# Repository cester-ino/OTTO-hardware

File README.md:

## OTTO-project
Hardware prototype for the [OTTO Synthesizer by Topisani](https://github.com/topisani/OTTO "OTTO Synthesizer by Topisani")

*10x10 silicone buttons with led backlight*

Main features

#### Mainboard
- ILI9341 based TFT 2.8" TFT screen.
- 4 low profile clickable encoders
- 40 function keys
- STM32F103VET6 mcu
- Raspberry GPIO connector
- connects to all the various boards
- expansion headers

#### Power board
- 2A 5-16V DC input & 500mah micro usb input
- [MAX8903A](https://datasheets.maximintegrated.com/en/ds/MAX8903-MAX8903Y.pdf "MAX8903A") 1s Lipo charger IC with path management
- 5V 2A DC-DC boost converter ([TPS61090](http://www.ti.com/lit/ds/symlink/tps61090.pdf "TPS61090")) & 3V3 700mah LDO ([XC6210](https://www.torexsemi.com/file/xc6210/XC6210.pdf "XC6210"))
- [MAX17048](https://datasheets.maximintegrated.com/en/ds/MAX17048-MAX17049.pdf "MAX17048") 1s lipo fuel gauge, connected via i2c to the raspberry
- [pi_power](https://github.com/craic/pi_power "pi_power") circuit for monitoring and control boot and shutdown routine

#### Audio Board
- SGTL5000 Audio Codec
- Electret microphone amp circuit
- LM4860 speaker amplifier
- 1 TRS jack line IN
- 1 TRS jack line OUT
- 1 Headphone IN

#### Keyboard
- 2 octaves keyboard with 16 keys bottom row
- expansion headers
- 16 addressable rgb leds

those specs refer to the tactile buttons version, but a led backlight button version is in the works too.

*one of the first design iteration*

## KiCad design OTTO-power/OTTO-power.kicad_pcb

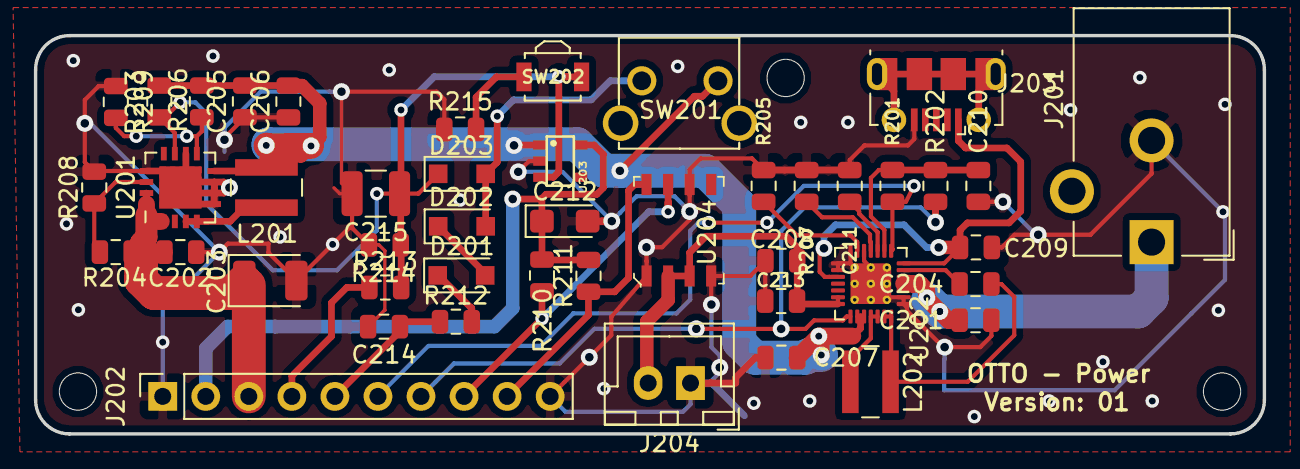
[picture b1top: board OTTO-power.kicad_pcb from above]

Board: 2 copper layers, 72.5 x 23.5 mm, 45 parts (0 on the bottom side), 28 nets.

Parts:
C201, C202, C210: 2.2uf; C_0805_2012Metric
C203: 100uf; CP_EIA-3528-21_Kemet-B
C204: 1uf; C_0805_2012Metric
C205, C207, C208: 10uf; C_0805_2012Metric
C206, C213, C214: 0.1uf; C_0805_2012Metric
C209: 4.7uf; C_0805_2012Metric
C211: 0.15uf; C_0805_2012Metric
C212: 10uf; CP_EIA-3216-18_Kemet-A
C215: 100uf; C_1210_3225Metric
D201, D202, D203: IN4001; D_SOD-123F
J201: Barrel_Jack; BarrelJack_CUI_PJ-102AH_Horizontal
J202: Conn_01x10; PinSocket_1x10_P2.54mm_Vertical
J203: USB_B_Micro; USB_Micro-B_Molex-105017-0001
J204: battery; JST_XH_B02B-XH-A_1x02_P2.50mm_Vertical
L201: 6.8uH; L_Wuerth_MAPI-4020
L202: 3.3uH; L_Wuerth_MAPI-4020
R201, R202, R210, R211, R214: 100K; R_0805_2012Metric
R203, R208: 200K; R_0805_2012Metric
R204, R206: 1.87M; R_0805_2012Metric
R205: 1.2K; R_0805_2012Metric
R207: 3K; R_0805_2012Metric
R209: 340K; R_0805_2012Metric
R212, R213: 10K; R_0805_2012Metric
R215: 1K; R_0805_2012Metric
SW201: SW_Push; SKHHLVA010
SW202: SW_reset; SW_SPST_B3U-3000P
U201: TPS61090; QFN-16-1EP_4x4mm_P0.65mm_EP2.5x2.5mm
U202: MAX8903A; QFN-28-1EP_4x4mm_P0.4mm_EP2.4x2.4mm_ThermalVias
U203: XC6210; SOT25
U204: MAX17048; TDFN-8-1EP

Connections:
3V3: C212.1, J202.2, R210.2, R211.2, U203.5
5V: C202.2, C203.1, J202.3, R204.2, U201.1, U201.15, U201.16
BATT+: C208.2, C213.2, J204.2, U202.20, U202.21, U204.2, U204.3
CHG_OUT: J202.7, R202.1, U202.22
DC: C201.1, J201.1, U202.3, U202.4, U202.5
DOK_OUT: J202.6, R201.1, U202.8
EN_PI: C215.1, D203.1, R203.1, R213.1, R214.2, SW202.2, U201.11, U203.3
GNDA: C201.2, C202.1, C203.2, C205.1, C206.1, C207.1, C208.1, C209.1, C210.1, C211.1, C212.2, C213.1, C214.2, C215.2, J201.2, J202.1, J202.10, J203.5, J204.1, R205.1, R207.1, R208.1, R209.1, R214.1, R215.1, U201.5, U201.6, U201.7, U201.10, U201.13, U201.17, U202.1, U202.2, U202.12, U202.14, U202.15, U202.16, U202.29, U203.2, U204.1, U204.4, U204.6
unnamed: C204.1, U202.6
unnamed: C204.2, L202.2, U202.27, U202.28
unnamed: C211.2, U202.10
unnamed: D201.1, R212.1
unnamed: D201.2, D202.1
unnamed: D202.2, D203.2, SW201.2
unnamed: L201.1, U201.3, U201.4
unnamed: L202.1, U202.25, U202.26
unnamed: R204.1, R208.2, U201.14
unnamed: R205.2, U202.13
unnamed: R206.1, R209.2, U201.9
unnamed: R207.2, U202.11
unnamed: R215.2, SW202.1
OUT_PIN: J202.4, R213.2
SCL: J202.8, R210.1, U204.7
SDA: J202.9, R211.1, U204.8
SENSE_PIN: C214.1, J202.5, R212.2
SYS: C205.2, C206.2, C207.2, L201.2, R203.2, R206.2, SW201.1, U201.8, U202.23, U202.24, U203.1
USB: C209.2, J203.1, U202.7, U202.17
VL: C210.2, R201.2, R202.2, U202.9

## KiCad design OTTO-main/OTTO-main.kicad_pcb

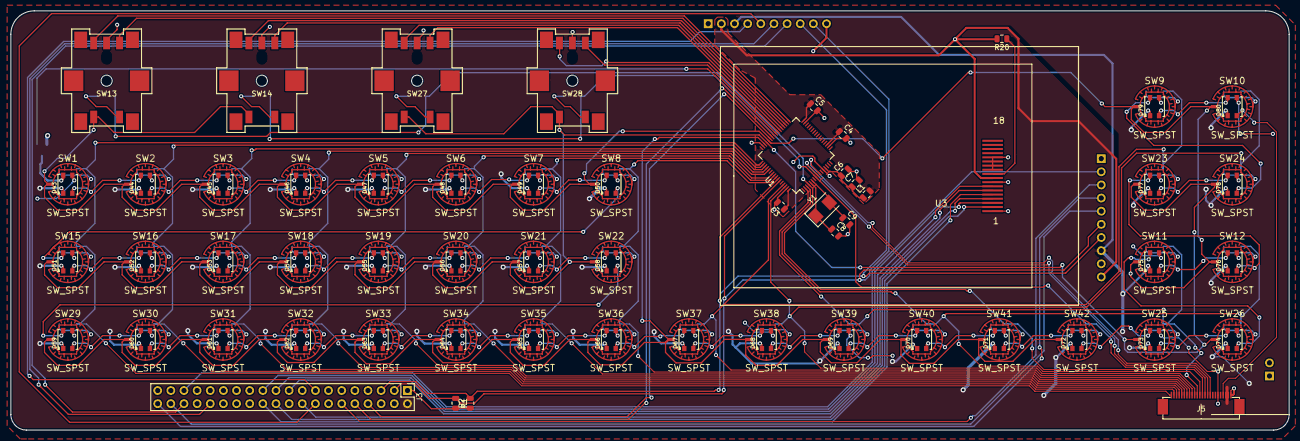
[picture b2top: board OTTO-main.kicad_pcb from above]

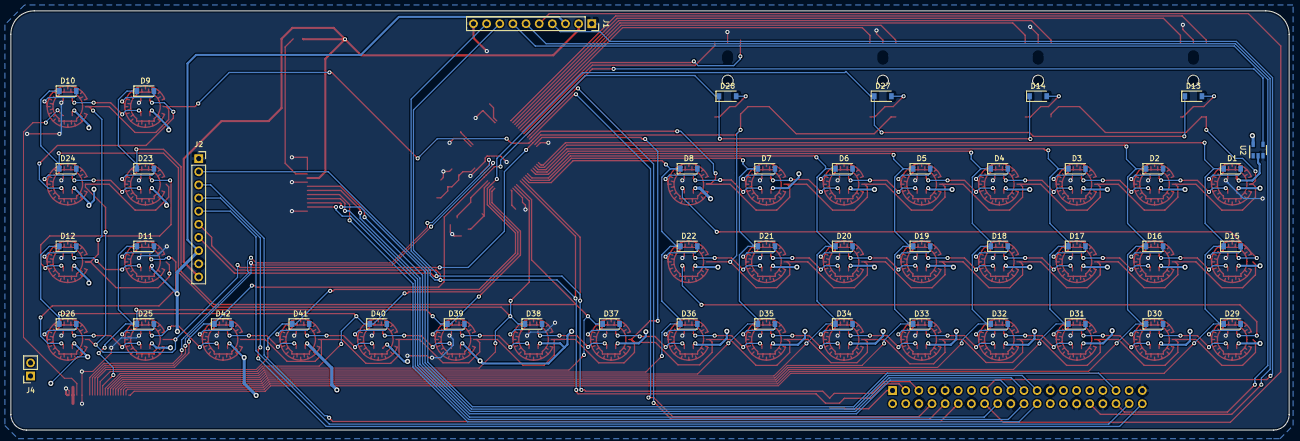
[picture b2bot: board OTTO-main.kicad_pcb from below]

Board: 4 copper layers, 247.0 x 81.0 mm, 142 parts (46 on the bottom side), 135 nets.

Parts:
C3, C4, C5, C6: 1uf; C_0805_2012Metric
C7: 10nf; C_0805_2012Metric
C8, C9: 22pf; C_0805_2012Metric
D1, D2, D3, D4, D5, D6, D7, D8, D9, D10, D11, D12, D15, D16, D17, D18, D19, D20, D21, D22, D23, D24, D25, D26, D29, D30, D31, D32, D33, D34, D35, D36, D37, D38, D39, D40, D41, D42: D_ALT; D_SOD-123
D13, D14, D27, D28: 1N4148; D_SOD-123
D43, D44, D45, D46, D47, D48, D49, D50, D51, D52, D53, D54, D55, D56, D57, D58, D59, D60, D61, D62, D63, D64, D65, D66, D67, D68, D69, D70, D71, D72, D73, D74, D75, D76, D77, D78, D79, D80: WS2812B; WS2812B_3535
J1: POWER_BOARD; PinSocket_1x10_P2.54mm_Vertical
J2: AUDIO_BOARD; PinSocket_1x10_P2.54mm_Vertical
J3: Raspberry_Pi_2_3; PinHeader_2x20_P2.54mm_Vertical
J4: MICROPHONE; PinSocket_1x02_P2.54mm_Vertical
J5: Conn_01x24; JUSHUO_AFC07-S24FCC-00
L1: 30ohm; C_0805_2012Metric
R1, R2: 4.7K; R_0805_2012Metric
R20: 3.9; R_0805_2012Metric
SW1, SW2, SW3, SW4, SW5, SW6, SW7, SW8, SW9, SW10, SW11, SW12, SW15, SW16, SW17, SW18, SW19, SW20, SW21, SW22, SW23, SW24, SW25, SW26, SW29, SW30, SW31, SW32, SW33, SW34, SW35, SW36, SW37, SW38, SW39, SW40, SW41, SW42: SW_SPST; SILICONE_BUTTON_10MM_4X4WIDE
SW13, SW14, SW27, SW28: Rotary_Encoder_Switch; PEC11S-929K-S0015
U1: STM32F103RETx; LQFP-64_10x10mm_P0.5mm
U2: 74AHCT1G125; SOT-23-5
U3: ILI9341; ILI_DISPLAY
Y1: 8mhz; Crystal_SMD_5032-2Pin_5.0x3.2mm

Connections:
3V3: C3.1, C4.1, C5.1, J1.2, J2.10, L1.2, R20.2, U1.19, U1.32, U1.48, U1.64, U3.9
5V: D43.1, D44.1, D45.1, D46.1, D47.1, D48.1, D49.1, D50.1, D51.1, D52.1, D53.1, D54.1, D55.1, D56.1, D57.1, D58.1, D59.1, D60.1, D61.1, D62.1, D63.1, D64.1, D65.1, D66.1, D67.1, D68.1, D69.1, D70.1, D71.1, D72.1, D73.1, D74.1, D75.1, D76.1, D77.1, D78.1, D79.1, D80.1, J1.3, J2.8, J3.2, J5.22, J5.23
BCLK: J2.3, J3.12
CE0: J3.24, U3.5
CHG_OUT: J1.7, J3.36
COL1: D1.1, D15.1, D29.1, J5.1, U1.49
COL2: D2.1, D16.1, D30.1, J5.2, U1.50
COL3: D3.1, D17.1, D31.1, J5.3, U1.51
COL4: D4.1, D18.1, D32.1, J5.4, U1.52
COL5: D5.1, D19.1, D33.1, J5.5, U1.53
COL6: D6.1, D20.1, D34.1, J5.6, U1.55
COL7: D7.1, D21.1, D35.1, J5.7, U1.56
COL8: D8.1, D22.1, D36.1, J5.8, U1.57
COL9: D9.1, D23.1, D37.1, J5.9, U1.61
COL10: D10.1, D24.1, D38.1, J5.10, U1.62
COL11: D11.1, D25.1, D39.1, J5.11, U1.2
COL12: D12.1, D26.1, D40.1, J5.12, U1.3
COL13: D13.1, D27.1, D41.1, J5.13, U1.4
COL14: D14.1, D28.1, D42.1, J5.14, U1.8
DOK_OUT: J1.6, J3.32
DOUT1: D52.2, D53.4
DOUT2: D66.2, D67.4
ENC1_A: SW13.A, U1.34
ENC1_B: SW13.B, U1.33
ENC2_A: SW14.A, U1.36
ENC2_B: SW14.B, U1.35
ENC3_A: SW27.A, U1.38
ENC3_B: SW27.B, U1.37
ENC4_A: SW28.A, U1.40
ENC4_B: SW28.B, U1.39
GND: C3.2, C4.2, C5.2, C6.2, C7.2, C8.2, C9.2, D43.3, D44.3, D45.3, D46.3, D47.3, D48.3, D49.3, D50.3, D51.3, D52.3, D53.3, D54.3, D55.3, D56.3, D57.3, D58.3, D59.3, D60.3, D61.3, D62.3, D63.3, D64.3, D65.3, D66.3, D67.3, D68.3, D69.3, D70.3, D71.3, D72.3, D73.3, D74.3, D75.3, D76.3, D77.3, D78.3, D79.3, D80.3, J1.1, J1.10, J2.1, J2.9, J3.6, J3.9, J3.14, J3.20, J3.25, J3.30, J3.34, J3.39, J5.19, J5.24, SW13.C, SW14.C, SW27.C, SW28.C, U1.12, U1.18, U1.31, U1.47, U1.63, U2.3, U3.1, U3.8, U3.11, U3.12, U3.13, U3.14
GPIO24: J3.18, U3.4
GPIO25: J3.22, U3.2
I2S_RX: J2.4, J3.40
I2S_TX: J2.5, J3.38
KBLED: D80.2, J5.21
LEDIN: U1.41, U2.4
LR_CLK: J2.2, J3.35
MISO_0: J3.21, U3.7
MOSI_0: J3.19, U3.6
unnamed: C6.1, C7.1, L1.1, U1.13
unnamed: D1.2, SW1.2
unnamed: D2.2, SW2.2
unnamed: D3.2, SW3.2
unnamed: D4.2, SW4.2
unnamed: D5.2, SW5.2
unnamed: D6.2, SW6.2
unnamed: D7.2, SW7.2
unnamed: D8.2, SW8.2
unnamed: D9.2, SW9.2
unnamed: D10.2, SW10.2
unnamed: D11.2, SW11.2
unnamed: D12.2, SW12.2
unnamed: D13.2, SW13.S1
unnamed: D14.2, SW14.S1
unnamed: D15.2, SW15.2
unnamed: D16.2, SW16.2
unnamed: D17.2, SW17.2
unnamed: D18.2, SW18.2
unnamed: D19.2, SW19.2
unnamed: D20.2, SW20.2
unnamed: D21.2, SW21.2
unnamed: D22.2, SW22.2
unnamed: D23.2, SW23.2
unnamed: D24.2, SW24.2
unnamed: D25.2, SW25.2
unnamed: D26.2, SW26.2
unnamed: D27.2, SW27.S1
unnamed: D28.2, SW28.S1
unnamed: D29.2, SW29.2
unnamed: D30.2, SW30.2
unnamed: D31.2, SW31.2
unnamed: D32.2, SW32.2
unnamed: D33.2, SW33.2
unnamed: D34.2, SW34.2
unnamed: D35.2, SW35.2
unnamed: D36.2, SW36.2
unnamed: D37.2, SW37.2
unnamed: D38.2, SW38.2
unnamed: D39.2, SW39.2
unnamed: D40.2, SW40.2
unnamed: D41.2, SW41.2
unnamed: D42.2, SW42.2
unnamed: D43.2, D44.4
unnamed: D43.4, U2.2
unnamed: D44.2, D45.4
unnamed: D45.2, D46.4
unnamed: D46.2, D47.4
unnamed: D47.2, D48.4
unnamed: D48.2, D49.4
unnamed: D49.2, D50.4
unnamed: D50.2, D51.4
unnamed: D51.2, D52.4
unnamed: D53.2, D54.4
unnamed: D54.2, D55.4
unnamed: D55.2, D56.4
unnamed: D56.2, D57.4
unnamed: D57.2, D58.4
unnamed: D58.2, D59.4
unnamed: D59.2, D60.4
unnamed: D60.2, D61.4
unnamed: D61.2, D62.4
unnamed: D62.2, D63.4
unnamed: D63.2, D64.4
unnamed: D64.2, D65.4
unnamed: D65.2, D66.4
unnamed: D67.2, D68.4
unnamed: D68.2, D69.4
unnamed: D69.2, D70.4
unnamed: D70.2, D71.4
unnamed: D71.2, D72.4
unnamed: D72.2, D73.4
unnamed: D73.2, D74.4
unnamed: D74.2, D75.4
unnamed: D75.2, D76.4
unnamed: D76.2, D77.4
unnamed: D77.2, D78.4
unnamed: D78.2, D79.4
unnamed: D79.2, D80.4
unnamed: J3.1, R1.2, R2.1
unnamed: R20.1, U3.10
OSC_IN: C8.1, U1.5, Y1.1
OSC_OUT: C9.1, U1.6, Y1.2
OUT_PIN: J1.4, J3.15
ROW1: SW1.1, SW2.1, SW3.1, SW4.1, SW5.1, SW6.1, SW7.1, SW8.1, SW9.1, SW10.1, SW11.1, SW12.1, SW13.S2, SW14.S2, U1.44
ROW2: SW15.1, SW16.1, SW17.1, SW18.1, SW19.1, SW20.1, SW21.1, SW22.1, SW23.1, SW24.1, SW25.1, SW26.1, SW27.S2, SW28.S2, U1.45
ROW3: SW29.1, SW30.1, SW31.1, SW32.1, SW33.1, SW34.1, SW35.1, SW36.1, SW37.1, SW38.1, SW39.1, SW40.1, SW41.1, SW42.1, U1.46
ROW4: J5.15, U1.9
ROW5: J5.16, U1.10
SCL: J1.8, J2.7, J3.5, R2.2, U1.58
SCLK_0: J3.23, U3.3
SDA: J1.9, J2.6, J3.3, R1.1, U1.59
SENSE_PIN: J1.5, J3.16
UART_RXD: J3.10, U1.42
UART_TXD: J3.8, U1.43

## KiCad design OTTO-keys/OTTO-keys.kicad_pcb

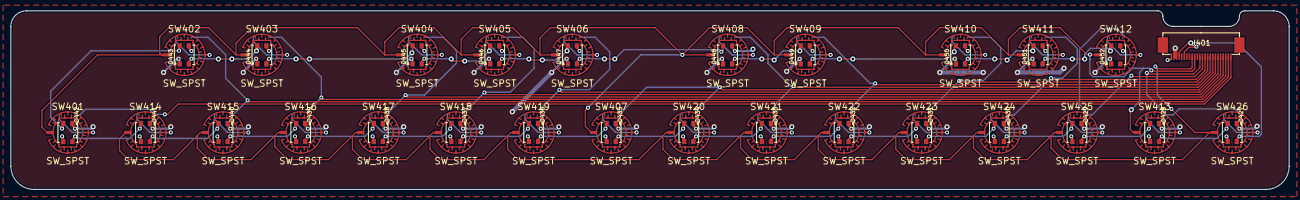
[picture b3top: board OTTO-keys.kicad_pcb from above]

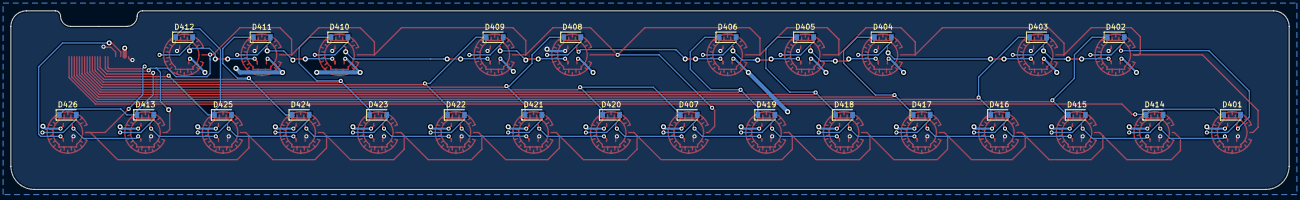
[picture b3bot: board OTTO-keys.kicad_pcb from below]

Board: 2 copper layers, 247.0 x 34.5 mm, 79 parts (26 on the bottom side), 69 nets.

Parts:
D401, D402, D403, D404, D405, D406, D407, D408, D409, D410, D411, D412, D413, D414, D415, D416, D417, D418, D419, D420, D421, D422, D423, D424, D425, D426: D_ALT; D_SOD-123
D427, D428, D429, D430, D431, D432, D433, D434, D435, D436, D437, D438, D439, D440, D441, D442, D443, D444, D445, D446, D447, D448, D449, D450, D451, D452: WS2812B; WS2812B_3535
J401: Conn_01x24; JUSHUO_AFC07-S24FCC-00
SW401, SW402, SW403, SW404, SW405, SW406, SW407, SW408, SW409, SW410, SW411, SW412, SW413, SW414, SW415, SW416, SW417, SW418, SW419, SW420, SW421, SW422, SW423, SW424, SW425, SW426: SW_SPST; SILICONE_BUTTON_10MM_4X4WIDE

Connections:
5V: D427.1, D428.1, D429.1, D430.1, D431.1, D432.1, D433.1, D434.1, D435.1, D436.1, D437.1, D438.1, D439.1, D440.1, D441.1, D442.1, D443.1, D444.1, D445.1, D446.1, D447.1, D448.1, D449.1, D450.1, D451.1, D452.1, J401.22, J401.23
COL1: D401.1, D414.1, J401.1
COL2: D402.1, D415.1, J401.2
COL3: D403.1, D416.1, J401.3
COL4: D404.1, D417.1, J401.4
COL5: D405.1, D418.1, J401.5
COL6: D406.1, D419.1, J401.6
COL7: D407.1, D420.1, J401.7
COL8: D408.1, D421.1, J401.8
COL9: D409.1, D422.1, J401.9
COL10: D410.1, D423.1, J401.10
COL11: D411.1, D424.1, J401.11
COL12: D412.1, D425.1, J401.12
COL13: D413.1, D426.1, J401.13
DOUT1: D440.2, D441.4
GND: D427.3, D428.3, D429.3, D430.3, D431.3, D432.3, D433.3, D434.3, D435.3, D436.3, D437.3, D438.3, D439.3, D440.3, D441.3, D442.3, D443.3, D444.3, D445.3, D446.3, D447.3, D448.3, D449.3, D450.3, D451.3, D452.3, J401.19, J401.24
KBLED: D427.4, J401.21
unnamed: D401.2, SW401.2
unnamed: D402.2, SW402.2
unnamed: D403.2, SW403.2
unnamed: D404.2, SW404.2
unnamed: D405.2, SW405.2
unnamed: D406.2, SW406.2
unnamed: D407.2, SW407.2
unnamed: D408.2, SW408.2
unnamed: D409.2, SW409.2
unnamed: D410.2, SW410.2
unnamed: D411.2, SW411.2
unnamed: D412.2, SW412.2
unnamed: D413.2, SW413.2
unnamed: D414.2, SW414.2
unnamed: D415.2, SW415.2
unnamed: D416.2, SW416.2
unnamed: D417.2, SW417.2
unnamed: D418.2, SW418.2
unnamed: D419.2, SW419.2
unnamed: D420.2, SW420.2
unnamed: D421.2, SW421.2
unnamed: D422.2, SW422.2
unnamed: D423.2, SW423.2
unnamed: D424.2, SW424.2
unnamed: D425.2, SW425.2
unnamed: D426.2, SW426.2
unnamed: D427.2, D428.4
unnamed: D428.2, D429.4
unnamed: D429.2, D430.4
unnamed: D430.2, D431.4
unnamed: D431.2, D432.4
unnamed: D432.2, D433.4
unnamed: D433.2, D434.4
unnamed: D434.2, D435.4
unnamed: D435.2, D436.4
unnamed: D436.2, D437.4
unnamed: D437.2, D438.4
unnamed: D438.2, D439.4
unnamed: D439.2, D440.4
unnamed: D441.2, D442.4
unnamed: D442.2, D443.4
unnamed: D443.2, D444.4
unnamed: D444.2, D445.4
unnamed: D445.2, D446.4
unnamed: D446.2, D447.4
unnamed: D447.2, D448.4
unnamed: D448.2, D449.4
unnamed: D449.2, D450.4
unnamed: D450.2, D451.4
unnamed: D451.2, D452.4
ROW4: J401.15, SW401.1, SW402.1, SW403.1, SW404.1, SW405.1, SW406.1, SW407.1, SW408.1, SW409.1, SW410.1, SW411.1, SW412.1, SW413.1
ROW5: J401.16, SW414.1, SW415.1, SW416.1, SW417.1, SW418.1, SW419.1, SW420.1, SW421.1, SW422.1, SW423.1, SW424.1, SW425.1, SW426.1

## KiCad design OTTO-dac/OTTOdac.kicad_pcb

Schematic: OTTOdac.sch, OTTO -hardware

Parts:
C101, C104, C106, C109, C110, C112, C113, C119: 2.2uf; C_0805_2012Metric
C102, C103, C105, C108, C117, C118: 0.1uf; C_0805_2012Metric
C107, C116: 0.1uf; CP_EIA-2012-12_Kemet-R
C111: 1uf; CP_EIA-3216-18_Kemet-A
C114, C115: 220uf; CP_Elec_5x5.9
J101: SJ1-42536-SMT; PJ-393-7A; MPN SJ1-42536-SMT
J102: Audio_IN; PJ-237-6A
J103: Audio_OUT; PJ-237-6A
J104: Speaker; JST_XH_B02B-XH-A_1x02_P2.50mm_Vertical; MPN XH-B02B
J105: Conn_01x10; PinHeader_1x10_P2.54mm_Vertical
L101: 600; Fuse_0805_2012Metric
MK101: Microphone; PinHeader_1x02_P2.54mm_Vertical
R101, R102: 100K; R_0805_2012Metric
R103, R105: 10K; R_0805_2012Metric
R104, R106, R107: 1K; R_0805_2012Metric
R108: 2.2K; R_0805_2012Metric
U101: AMS1117-3.3; SOT-223-3_TabPin2
U102: SGTL5000; QFN-32-NXP-SGTL5000
X101: XO32; Oscillator_SMD_Abracon_ASV-4Pin_7.0x5.1mm

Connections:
+3V3: C101.1, C102.1, C103.1, C108.1, J105.10, L101.1, U101.3 (VI), U102.20, X101.1, X101.4
+5V: C107.1, J105.8, R101.1; also elsewhere on the board
GNDREF: C101.2, C102.2, C103.2, C104.2, C105.2, C106.2, C107.2, C108.2, C116.2, C117.1, C119.2, J101.4, J102.1, J103.1, J105.1, J105.9, MK101.1, R107.1, U101.1 (GND), U102.1, U102.3, U102.7, U102.31, U102.32, U102.33, X101.2; also elsewhere on the board
HPL: C114.2, J101.2, R104.1
HPR: C115.2, J101.3, R106.1, R107.2
MIC: C118.2, J101.1, R108.2
unnamed: C104.1, C105.1, L101.2, U102.5
unnamed: C106.1, U101.2 (VO), U102.30
unnamed: C109.1, U102.14
unnamed: C109.2, J102.2
unnamed: C110.1, U102.13
unnamed: C110.2, J102.3
unnamed: C111.1, R105.1
unnamed: C111.2, R104.2, R106.2
unnamed: C112.1, U102.11
unnamed: C112.2, J103.3
unnamed: C113.1, U102.12
unnamed: C113.2, J103.2
unnamed: C114.1, U102.6
unnamed: C115.1, U102.2
unnamed: C117.2, U102.10
unnamed: C118.1, U102.15
unnamed: C119.1, R108.1, U102.16
unnamed: J101.6, R101.2, R102.2
unnamed: J101.8, MK101.2
unnamed: R103.2, R105.2
unnamed: U102.21, X101.3
PIN3: J105.6, U102.27
PIN5: J105.7, U102.29
PIN12: J105.3, U102.24
PIN35: J105.2, U102.23
PIN38: J105.5, U102.26
PIN40: J105.4, U102.25

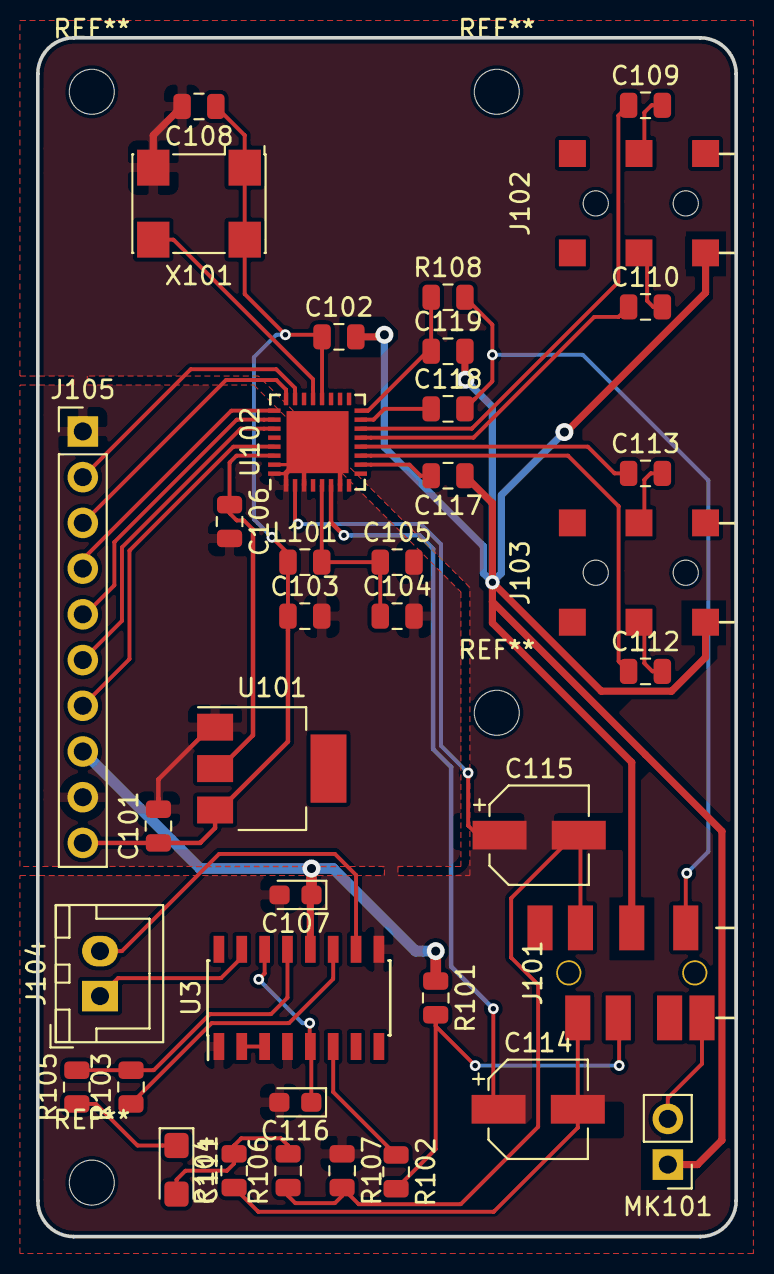
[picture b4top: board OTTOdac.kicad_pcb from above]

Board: 2 copper layers, 38.8 x 66.6 mm, 38 parts (0 on the bottom side), 35 nets.

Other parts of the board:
U3: LM4860; SOIC-16_3.9x9.9mm_P1.27mm

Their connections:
+5V: U3.12; also elsewhere on the board
GNDREF: U3.1, U3.4, U3.9; also elsewhere on the board
unnamed: U3.5, U3.14
unnamed: U3.2, U3.3

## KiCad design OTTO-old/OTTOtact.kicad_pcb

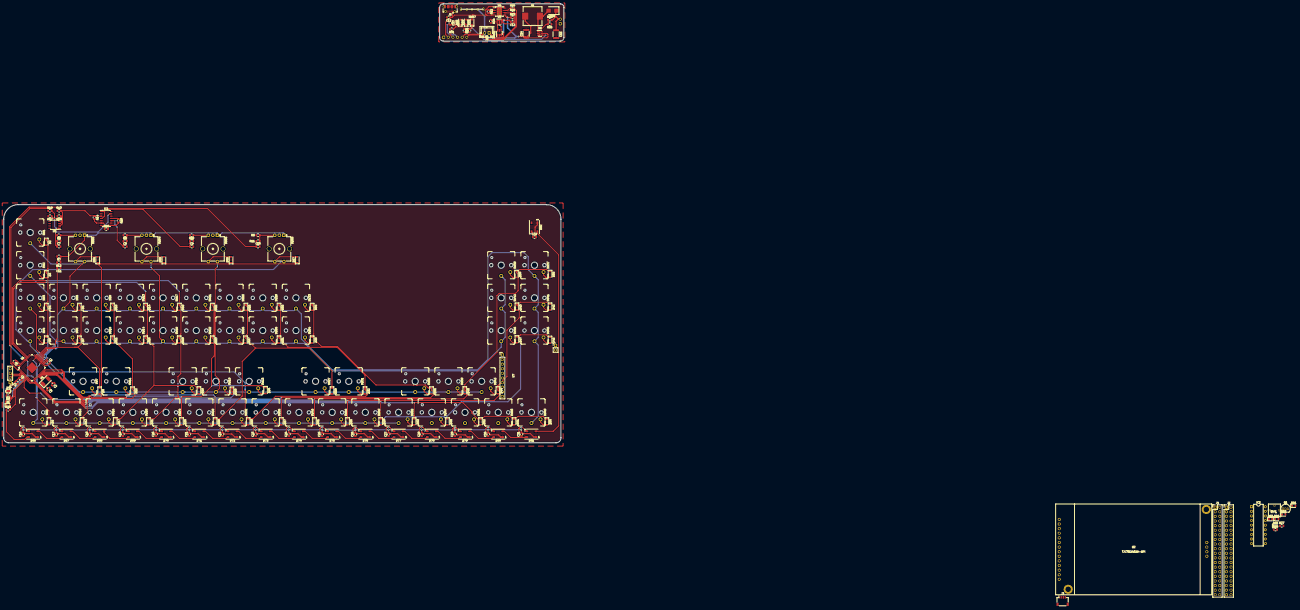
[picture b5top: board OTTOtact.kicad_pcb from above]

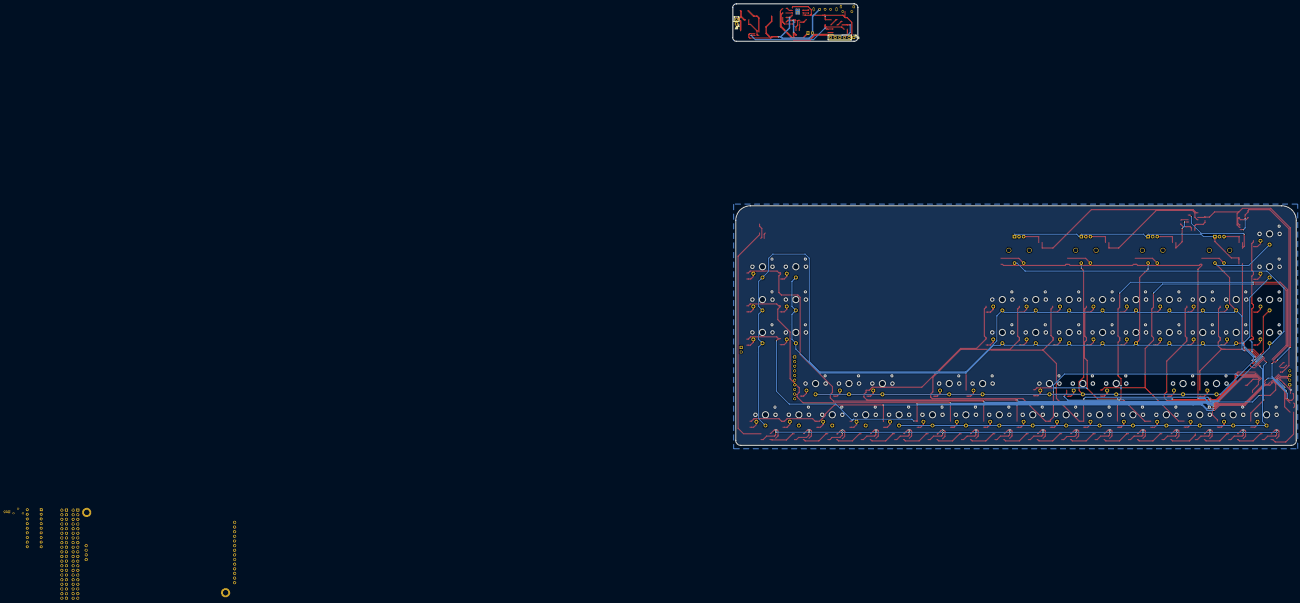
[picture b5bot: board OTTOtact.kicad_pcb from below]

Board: 2 copper layers, 307.0 x 131.2 mm, 229 parts (2 on the bottom side), 184 nets.

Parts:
C1, C5, C6, C7, C8, C9, C10, C11, C13, C33, C34: 0.1uF; C_0805_2012Metric
C2: 1uF; C_0805_2012Metric
C3, C4: 22pF; C_0805_2012Metric
C12: 10uF; C_0805_2012Metric
C14, C15: 22uF; C_1812_4532Metric
C16, C17, C18, C19, C20, C21, C22, C23, C24, C25, C26, C27, C28, C29, C30, C31, C32: 0.1uf; C_0805_2012Metric
D1: LED; LED_0805_2012Metric
D2, D3, D4, D5, D6, D7, D8, D9, D10, D11, D12, D13, D14, D15, D16, D17, D18, D19, D20, D21, D22, D23, D24, D25, D26, D27, D28, D29, D30, D31, D32, D33, D34, D35, D36, D37, D38, D39, D40, D41, D42, D43, D44, D45, D46, D47, D48, D49, D50, D51, D52, D53, D54, D55, D56, D57: 1N4148; D_SOD-123v
D60: SS34; D_SMB
D61, D62, D63, D64, D65: LED_Small; LED_0805_2012Metric
D66, D67, D68, D69, D70, D71, D72, D73, D74, D75, D76, D77, D78, D79, D80, D81, D82: WS2812B; LED_WS2812B_PLCC4_5.0x5.0mm_P3.2mm
D83, D84, D85: IN4001; D_SOD-123F
IC1: 74HC125; SOIC-14_3.9x8.7mm_P1.27mm
IC2: LM3914; DIP-18_W7.62mm
J1: USB; PinHeader_1x04_P2.54mm_Vertical
J2: gpio_exp2; PinHeader_2x20_P2.54mm_Vertical
J3: Conn_01x04_Male; JST_SH_SM04B-SRSS-TB_1x04-1MP_P1.00mm_Horizontal
J4: gpio_exp1; PinHeader_2x20_P2.54mm_Vertical
J5: USB_B_Micro; USB_Micro-B_Molex-105017-0001
J6: battery; JST_XH_B02B-XH-A_1x02_P2.50mm_Vertical
J7: Conn_01x06; PinHeader_1x06_P2.54mm_Vertical
J8: Conn_01x02; PinHeader_1x02_P2.54mm_Vertical
JP1: SolderJumper_2_Open; SolderJumper-2_P1.3mm_Open_RoundedPad1.0x1.5mm
L1: 22uH; L_Wuerth_HCI-1040
M1: FS8205; SOT-23-6_Handsoldering
Q1: 2N7000; TO-92_Inline
R1, R3, R4, R5, R6, R7, R8, R9, R10, R11, R12, R30, R31, R32: 10K; R_0805_2012Metric
R2: 330K; R_0805_2012Metric
R13, R15: 1.5K; R_0805_2012Metric
R14: 470K; R_0805_2012Metric
R16: 820K; R_0805_2012Metric
R17, R19, R20, R21, R26: 1K; R_0805_2012Metric
R18: 15K; R_0805_2012Metric
R22: 2k; R_0805_2012Metric
R23, R28: 100K; R_0805_2012Metric
R24: 2.7k; R_0805_2012Metric
R25: 7.5K; R_0805_2012Metric
R27: 4.7K; R_0805_2012Metric
R29: 330; R_0805_2012Metric
RV1: 10K; 3362P_1
SW1, SW2, SW3, SW4, SW5, SW6, SW7, SW8, SW9, SW10, SW11, SW12, SW13, SW14, SW15, SW16, SW17, SW18, SW19, SW20, SW21, SW22, SW23, SW24, SW25, SW26, SW27, SW28, SW29, SW30, SW31, SW32, SW33, SW34, SW35, SW36, SW37, SW38, SW39, SW40, SW41, SW42, SW43, SW44, SW45, SW46, SW47, SW48, SW49, SW50, SW51, SW52: SW_Push; kaihl-low-profile-switch-noled
SW53, SW54, SW55, SW56: Rotary_Encoder_Switch; RotaryEncoder_Alps_EC12E-Switch_Vertical_H20mm_CircularMoun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
SW57: ON_OFF_SWITCH; SK-12E12-G5
U1: ATMEGA32U4-AU; TQFP-44-1EP_10x10mm_P0.8mm_EP4.5x4.5mm
U2: TJCTM24028-SPI
U3: MCP602; SOIC-8_3.9x4.9mm_P1.27mm
U4: TP4056; Texas_HTSOP-8-1EP_3.9x4.9mm_P1.27mm_EP2.95x4.9mm_Mask2.4x3.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
U5: FS312F-G; SOT-23-6
U6: MT3608; SOT-23-6
U7: OTTO-dac; OTTO_DACv0.1
Y1: 16mhz; Crystal_SMD_Abracon_ABM3-2Pin_5.0x3.2mm

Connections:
5V: C15.1, D60.1, J8.2, R25.2
36: J2.36, J4.36, Q1.2, R28.1
+5V: C1.2, C5.1, C6.2, C16.2, C17.2, C18.2, C19.2, C20.2, C21.2, C22.2, C23.2, C24.2, C25.2, C26.2, C27.2, C28.2, C29.2, C30.2, C31.2, C32.2, D1.2, D66.1, D67.1, D68.1, D69.1, D70.1, D71.1, D72.1, D73.1, D74.1, D75.1, D76.1, D77.1, D78.1, D79.1, D80.1, D81.1, D82.1, IC1.2, IC1.5, IC1.7, IC1.9, IC1.12, J2.2, J4.2, R1.1, R3.2, R4.2, R5.2, R6.2, R7.2, R18.2, U1.2, U1.7, U1.14, U1.24, U1.34, U1.44, U7.8
-BATT: C13.2, J6.1, M1.3, U5.6
/gpio/1: J2.1, J3.2, J4.1, U2.1, U7.10
/gpio/3: J2.3, J3.3, J4.3, U7.6
/gpio/4: J2.4, J4.4
/gpio/5: J2.5, J3.4, J4.5, U7.7
/gpio/7: J2.7, J4.7
/gpio/8: J2.8, J4.8
/gpio/9: J2.9, J4.9
/gpio/11: J2.11, J4.11
/gpio/12: J2.12, J4.12, U2.8, U7.3
/gpio/13: J2.13, J4.13
/gpio/14: J2.14, J4.14
/gpio/15: J2.15, J4.15
/gpio/16: J2.16, J4.16
/gpio/17: J2.17, J4.17
/gpio/18: J2.18, J4.18, U2.5
/gpio/19: J2.19, J4.19, U2.6
/gpio/20: J2.20, J4.20
/gpio/21: J2.21, J4.21, U2.9
/gpio/22: J2.22, J4.22, U2.4
/gpio/23: J2.23, J4.23, U2.7
/gpio/24: J2.24, J4.24, U2.3
/gpio/25: J2.25, J4.25
/gpio/26: J2.26, J4.26
/gpio/27: J2.27, J4.27
/gpio/28: J2.28, J4.28
/gpio/29: J2.29, J4.29
/gpio/30: J2.30, J4.30
/gpio/31: J2.31, J4.31
/gpio/32: J2.32, J4.32
/gpio/33: J2.33, J4.33
/gpio/34: J2.34, J4.34
/gpio/35: J2.35, J4.35, U7.2
/gpio/37: J2.37, J4.37
/gpio/38: J2.38, J4.38, U7.5
/gpio/39: J2.39, J4.39
/gpio/40: J2.40, J4.40, U7.4
BATT: C14.1, D61.2, D62.2, D63.2, D64.2, D65.2, IC2.3, IC2.9, J6.2, L1.1, R23.1, R27.2, SW57.3, U4.5, U6.5
COL1: D2.1, D3.1, D4.1, D5.1, U1.29
COL2: D6.1, D7.1, D8.1, D9.1, U1.31
COL3: D10.1, D11.1, D12.1, D13.1, U1.32
COL4: D14.1, D15.1, D16.1, D17.1, U1.36
COL5: D18.1, D19.1, D20.1, D21.1, U1.37
COL6: D22.1, D23.1, D24.1, D25.1, U1.22
COL7: D26.1, D27.1, D28.1, D29.1, U1.21
COL8: D30.1, D31.1, D32.1, D33.1, U1.20
COL9: D34.1, D35.1, D36.1, D37.1, U1.19
COL10: D38.1, D39.1, D40.1, D41.1, U1.18
COL11: D42.1, D43.1, D44.1, D45.1, U1.12
COL12: D46.1, D47.1, D48.1, D49.1, U1.11
COL13: D50.1, D51.1, D52.1, D53.1, U1.10
COL14: D54.1, D55.1, D56.1, D57.1, U1.9
D+: J1.2, U1.4
D-: J1.3, U1.3
EN: C34.1, D85.1, R31.1, R32.2, U6.4
GNDREF: C1.1, C2.2, C3.2, C4.2, C5.2, C6.1, C7.2, C8.2, C9.2, C10.2, C11.2, C12.2, C14.2, C15.2, C16.1, C17.1, C18.1, C19.1, C20.1, C21.1, C22.1, C23.1, C24.1, C25.1, C26.1, C27.1, C28.1, C29.1, C30.1, C31.1, C32.1, C33.1, C34.2, D66.3, D67.3, D68.3, D69.3, D70.3, D71.3, D72.3, D73.3, D74.3, D75.3, D76.3, D77.3, D78.3, D79.3, D80.3, D81.3, D82.3, IC1.14, J1.1, J2.6, J3.1, J4.6, J5.5, J5.6, J7.1, J8.1, JP1.2, M1.1, Q1.1, R13.1, R17.2, R19.1, R22.2, R24.2, R26.1, R28.2, R32.1, SW53.C, SW54.C, SW55.C, SW56.C, U1.5, U1.15, U1.23, U1.33, U1.35, U1.43, U1.45, U2.2, U4.1, U4.3, U4.9, U6.2, U7.1, U7.9
LED: R29.2, U1.8
LED_G: J7.5, R21.2
LED_POW: C12.1, J5.1, J7.2, U4.4, U4.8
LED_R: J7.6, R20.2
unnamed: C2.1, U1.17, Y1.2
unnamed: C3.1, U1.16, Y1.1
unnamed: C4.1, U1.6
unnamed: C7.1, IC1.13, R8.1
unnamed: C8.1, IC1.10, R9.1
unnamed: C9.1, IC1.4, R10.1
unnamed: C10.1, IC1.1, R11.1
unnamed: C13.1, R23.2, U5.5
unnamed: D1.1, R2.1
unnamed: D2.2, SW1.2
unnamed: D3.2, SW2.2
unnamed: D4.2, SW3.2
unnamed: D5.2, SW4.2
unnamed: D6.2, SW5.2
unnamed: D7.2, SW6.2
unnamed: D8.2, SW7.2
unnamed: D9.2, SW8.2
unnamed: D10.2, SW9.2
unnamed: D11.2, SW10.2
unnamed: D12.2, SW11.2
unnamed: D13.2, SW12.2
unnamed: D14.2, SW13.2
unnamed: D15.2, SW14.2
unnamed: D16.2, SW15.2
unnamed: D17.2, SW16.2
unnamed: D18.2, SW17.2
unnamed: D19.2, SW18.2
unnamed: D20.2, SW19.2
unnamed: D21.2, SW20.2
unnamed: D22.2, SW21.2
unnamed: D23.2, SW22.2
unnamed: D24.2, SW23.2
unnamed: D25.2, SW24.2
unnamed: D26.2, SW25.2
unnamed: D27.2, SW26.2
unnamed: D28.2, SW27.2
unnamed: D29.2, SW28.2
unnamed: D30.2, SW29.2
unnamed: D31.2, SW30.2
unnamed: D32.2, SW31.2
unnamed: D33.2, SW32.2
unnamed: D34.2, SW33.2
unnamed: D35.2, SW34.2
unnamed: D36.2, SW35.2
unnamed: D37.2, SW36.2
unnamed: D38.2, SW37.2
unnamed: D39.2, SW38.2
unnamed: D40.2, SW39.2
unnamed: D41.2, SW40.2
unnamed: D42.2, SW41.2
unnamed: D43.2, SW42.2
unnamed: D44.2, SW43.2
unnamed: D45.2, SW44.2
unnamed: D46.2, SW45.2
unnamed: D47.2, SW46.2
unnamed: D48.2, SW47.2
unnamed: D49.2, SW48.2
unnamed: D50.2, SW49.2
unnamed: D51.2, SW50.2
unnamed: D52.2, SW51.2
unnamed: D53.2, SW52.2
unnamed: D54.2, SW53.S2
unnamed: D55.2, SW54.S2
unnamed: D56.2, SW55.S2
unnamed: D57.2, SW56.S2
unnamed: D60.2, L1.2, U6.1
unnamed: D61.1, IC2.18
unnamed: D62.1, IC2.16
unnamed: D63.1, IC2.14
unnamed: D64.1, IC2.12
unnamed: D65.1, IC2.10
unnamed: D66.2, D67.4
unnamed: D66.4, R29.1
unnamed: D67.2, D68.4
unnamed: D68.2, D69.4
unnamed: D69.2, D70.4
unnamed: D70.2, D71.4
unnamed: D71.2, D72.4
unnamed: D72.2, D73.4
unnamed: D73.2, D74.4
unnamed: D74.2, D75.4
unnamed: D75.2, D76.4
unnamed: D76.2, D77.4
unnamed: D77.2, D78.4
unnamed: D78.2, D79.4
unnamed: D79.2, D80.4
unnamed: D80.2, D81.4
unnamed: D81.2, D82.4
unnamed: D83.1, R30.1
unnamed: D83.2, D84.1
unnamed: D84.2, D85.2, SW57.2
unnamed: IC1.6, R14.2, R16.1
unnamed: IC1.8, R15.2, R16.2
unnamed: IC1.11, R15.1
unnamed: IC2.2, IC2.4, IC2.8, Q1.3, R27.1, RV1.3
unnamed: IC2.5, RV1.2
unnamed: IC2.6, IC2.7, RV1.1
unnamed: M1.4, U5.1
unnamed: M1.6, U5.3
unnamed: R2.2, U1.38
unnamed: R3.1, R8.2, SW53.B
unnamed: R4.1, R9.2, SW54.B
unnamed: R5.1, R10.2, SW55.B
unnamed: R6.1, R11.2, SW56.B
unnamed: R7.1, R12.2, SW53.A, SW54.A, SW55.A, SW56.A
unnamed: R17.1, R18.1, U3.3
unnamed: R20.1, U4.7
unnamed: R21.1, U4.6
unnamed: R22.1, U4.2
unnamed: R24.1, U5.2
unnamed: R25.1, R26.2, U6.3
OUT_PIN: J7.3, R31.2
PD4: C11.1, R12.1, U1.25
PE6: R19.2, U1.1, U3.1
PF4: IC1.3, R13.2, R14.1, U1.39, U3.2
RESET: JP1.1, R1.2, U1.13
ROW1: SW1.1, SW5.1, SW9.1, SW13.1, SW17.1, SW21.1, SW25.1, SW29.1, SW33.1, SW37.1, SW41.1, SW45.1, SW49.1, SW53.S1, U1.30
ROW2: SW2.1, SW6.1, SW10.1, SW14.1, SW18.1, SW22.1, SW26.1, SW30.1, SW34.1, SW38.1, SW42.1, SW46.1, SW50.1, SW54.S1, U1.28
ROW3: SW3.1, SW7.1, SW11.1, SW15.1, SW19.1, SW23.1, SW27.1, SW31.1, SW35.1, SW39.1, SW43.1, SW47.1, SW51.1, SW55.S1, U1.27
ROW4: SW4.1, SW8.1, SW12.1, SW16.1, SW20.1, SW24.1, SW28.1, SW32.1, SW36.1, SW40.1, SW44.1, SW48.1, SW52.1, SW56.S1, U1.26
SENSE_PIN: C33.2, J7.4, R30.2

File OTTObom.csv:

Refs,Value,Footprint,Quantity,MFR,MPN,SPR,SPN
SW55,ON_OFF_SWITCH,Button_Switch_THT:SW_E-Switch_EG1224_SPDT_Angled,1,E-Switch,EG1224,mouser,612-EG1224
SW8;SW7;SW11;SW12;SW15;SW19;SW23;SW27;SW30;SW34;SW36;SW37;SW39;SW43;SW47;SW50;SW18;SW22;SW26;SW33;SW35;SW38;SW42;SW46;SW3;SW4;SW2;SW1;SW5;SW6;SW10;SW14;SW17;SW9;SW13;SW16;SW49;SW45;SW41;SW40;SW44;SW48;SW31;SW28;SW24;SW29;SW25;SW21;SW20;SW32,SW_Push,Button_Switch_THT:Tactile_Switch_12x12x7.3_mm,50,-,-,-,-
C7;C11;C8;C9;C10;C13;C1;C6;C5,0.1uF,Capacitor_SMD:C_0805_2012Metric,9,-,-,-,-
C12,10uF,Capacitor_SMD:C_0805_2012Metric,1,-,-,-,-
C2,1uF,Capacitor_SMD:C_0805_2012Metric,1,-,-,-,-
C3;C4,22pF,Capacitor_SMD:C_0805_2012Metric,2,-,-,-,-
C14,22uF,Capacitor_SMD:C_0805_2012Metric,1,-,-,-,-
C19;C20,0.1uf,Capacitor_Tantalum_SMD:CP_EIA-2012-12_Kemet-R,2,-,-,-,-
C18,1uf,Capacitor_Tantalum_SMD:CP_EIA-2012-12_Kemet-R,1,-,-,-,-
C16;C17,220uf,Capacitor_Tantalum_SMD:CP_EIA-2012-12_Kemet-R,2,-,-,-,-
C15,22uF,Capacitor_Tantalum_SMD:CP_EIA-2012-12_Kemet-R,1,-,-,-,-
J10,Conn_01x04_Male,Connector_JST:JST_SH_SM04B-SRSS-TB_1x04-1MP_P1.00mm_Horizontal,1,-,-,-,-
J6,Speaker,Connector_JST:JST_XH_B02B-XH-A_1x02_P2.50mm_Vertical,1,JST,XH-B02B,-,-
J3,battery,Connector_JST:JST_XH_B02B-XH-A_1x02_P2.50mm_Vertical,1,JST,XH-B02B,-,-
J1,USB,Connector_PinHeader_2.54mm:PinHeader_1x04_P2.54mm_Vertical,1,-,1x04 pin header,-,-
J4,audio,Connector_PinHeader_2.54mm:PinHeader_1x04_P2.54mm_Vertical,1,-,1x04 pin header,-,-
J8,gpio_exp1,Connector_PinHeader_2.54mm:PinHeader_2x20_P2.54mm_Vertical,1,2x20 long pin header,-,-,-
J7,gpio_exp2,Connector_PinHeader_2.54mm:PinHeader_2x20_P2.54mm_Vertical,1,2x20 pin header,-,-,-
J2,USB_B_Micro,Connector_USB:USB_Micro-B_Molex-105017-0001,1,Molex,105017-0001,mouser,538-105017-0001
Y1,16mhz,Crystal:Crystal_SMD_Abracon_ABM3-2Pin_5.0x3.2mm,1,-,ABM3-16.000MHZ-D2Y-T,mouser,-
D58,SS34,Diode_SMD:D_SMC,1,-,SS34,mouser,512-SS34
D9;D8;D12;D13;D16;D20;D24;D28;D31;D35;D37;D38;D40;D44;D48;D51;D19;D23;D27;D34;D36;D39;D43;D47;D4;D5;D3;D2;D6;D7;D11;D15;D18;D10;D14;D17;D50;D46;D42;D41;D45;D49;D32;D29;D25;D30;D26;D22;D21;D33;D52;D53;D54;D55,1N4148,Diode_SMD:D_SOD-123v,54,-,1N4148W-E3-18,mouser,78-1N4148W-E3-18
U7,CR2013-MI2120,Display:TJCTM24028-SPI,1,-,-,-,-
L1,22uH,Inductor_SMD:L_7.3x7.3_H4.5,1,Epcos,B82472G6223M000,mouser,871-B82472G6223M000
JP1,SolderJumper_2_Open,Jumper:SolderJumper-2_P1.3mm_Open_RoundedPad1.0x1.5mm,1,-,-,-,-
D1,LED,LED_SMD:LED_0805_2012Metric,1,-,HSMW-C170-U0000,-,-
D57,LEDG,LED_SMD:LED_0805_2012Metric,1,-,HSMQ-C170-T0000,-,-
D56,LEDR,LED_SMD:LED_0805_2012Metric,1,-,HSMC-C170-T0000,-,-
D59;D60;D61;D62;D63,LED_Small,LED_SMD:LED_0805_2012Metric,5,-,HSMW-C170-U0000,-,-
IC2,LM3914,Package_LCC:PLCC-20,1,-,LM3914VX/NOPB,mouser,926-LM3914VX/NOPB
U1,ATMEGA32U4-AU,Package_QFP:TQFP-44-1EP_10x10mm_P0.8mm_EP4.5x4.5mm,1,-,ATMEGA32U4-AU,-,556-ATMEGA32U4-AU
IC1,74HC125,Package_SO:SOIC-14_3.9x8.7mm_P1.27mm,1,-,SN74HC125DR,-,595-SN74HC125DR
U6,LM4860,Package_SO:SOIC-16_3.9x9.9mm_P1.27mm,1,-,LM4860MX/NOPB,-,-
U2,MCP602,Package_SO:SOIC-8_3.9x4.9mm_P1.27mm,1,-,MCP6022T-I/SN,-,-
U3,TP4056,Package_SO:Texas_HTSOP-8-1EP_3.9x4.9mm_P1.27mm_EP2.95x4.9mm_Mask2.4x3.1mm_ThermalVias,1,-,TP4056 SOP-8,-,-
U4,FS312F-G,Package_TO_SOT_SMD:SOT-23-6,1,-,FS312F-G SOT-23,-,-
U5,MT3608,Package_TO_SOT_SMD:SOT-23-6,1,-,MT3608 SOT-23,-,-
M1,FS8205,Package_TO_SOT_SMD:SOT-23-6_Handsoldering,1,-,FS8205 SOT-23,-,-
RV1,10K,Potentiometer_SMD:Potentiometer_Vishay_TS53YJ_Vertical,1,-,TS53YJ103MR10,-,-
R15;R13,1.5K,Resistor_SMD:R_0805_2012Metric,2,-,-,-,-
R23;R31;R32,100K,Resistor_SMD:R_0805_2012Metric,3,-,-,-,-
R1;R8;R3;R12;R7;R9;R4;R10;R5;R11;R6;R33;R34,10K,Resistor_SMD:R_0805_2012Metric,13,-,-,-,-
R18,15K,Resistor_SMD:R_0805_2012Metric,1,-,-,-,-
R17;R19;R21;R20;R26;R30;R29;R28,1K,Resistor_SMD:R_0805_2012Metric,8,-,-,-,-
R24,2.7k,Resistor_SMD:R_0805_2012Metric,1,-,-,-,-
R22,2k,Resistor_SMD:R_0805_2012Metric,1,-,-,-,-
R2,330K,Resistor_SMD:R_0805_2012Metric,1,-,-,-,-
R27,4.7K,Resistor_SMD:R_0805_2012Metric,1,-,-,-,-
R14,470K,Resistor_SMD:R_0805_2012Metric,1,-,-,-,-
R25,7.5K,Resistor_SMD:R_0805_2012Metric,1,-,-,-,-
R16,820K,Resistor_SMD:R_0805_2012Metric,1,-,-,-,-
SW51;SW52;SW53;SW54,Rotary_Encoder_Switch,Rotary_Encoder:RotaryEncoder_Alps_EC12E-Switch_Vertical_H20mm_CircularMountingHoles,4,-,EC12D1564404,-,-
J5,SJ1-42536-SMT,SJ1:CUI_SJ1-42536-SMT,1,Cui,SJ1-42536-SMT,mouser, 490-SJ1-42536-SMT-TR

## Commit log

2018-08-03 added images and started writing the readme
2018-08-03 readme edit
2018-08-03 moved USB connector
2018-08-05 redesigned the whole audio amplifier circuit, now the headphone switch should work
2018-08-07 rewired atmega
2018-08-10 annotation changes - preliminary BOM added
2018-08-13 display footprint, bom update
2018-08-25 0.1v rellease
2018-09-24 merged the dev repo with the local
2018-09-24 added some images
2018-09-24 no message
2018-09-24 corrected img link
2018-09-27 added a reset button to the power board
2018-09-27 Revert "added a reset button to the power board"
    This reverts commit bbfaa2fb8df27d7f63d1a584e9f51fc8f5fa6fe3.
2018-09-27 Revert "Revert "added a reset button to the power board""
    This reverts commit f20825db904c66ff1a5b44b22e19a70ce58abb56.
2018-10-01 progresses in the mainboard wiring
2018-10-01 re-wired the stm32 to optimize the routing
2018-10-09 added the OTTO-Keys board and fixed some of the mainboard issues
2018-10-11 added the OTTO-keys files
2018-11-18 Add files via upload
    Attempted to consolidate some of the traces and component placement for the OTTO power board. Only current outstanding item is double checking via sizing for max current load and overall QA check of 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
